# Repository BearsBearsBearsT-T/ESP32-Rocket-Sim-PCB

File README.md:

# ESP32-Rocket-Sim-PCB
An MPU and ESP32 powered PCB that tracks motion in real time useing an MPU 6050 and an ESP32-c3-wroom made in KICAD. This bored can senses movement, orientation, and rotation by reading accelerometer and gyroscope data from the MPU. I made this project to learn more about digital sensors and building somthing with out a tutorial. 

**What it does:**
- It uses the MPU 6050 to track motion and orientation and controld the orientation of a rocket graphic made in processing (soming soon)
- powerd by a USB-C (V2 might be whireless)
- Runs on ESP32

**Componants:**

- ESP32
- MPU6050
- USB-C
- Voltage regulator
- capasators

This was my 2nd ever PCB and I think this one is a really cool project. I like sensors alot and I like making hardware that interacts with software. 
This was my first PCB that was not from a tutorial and the process was suppriseingly intuative. 

# Pictures

# BOM

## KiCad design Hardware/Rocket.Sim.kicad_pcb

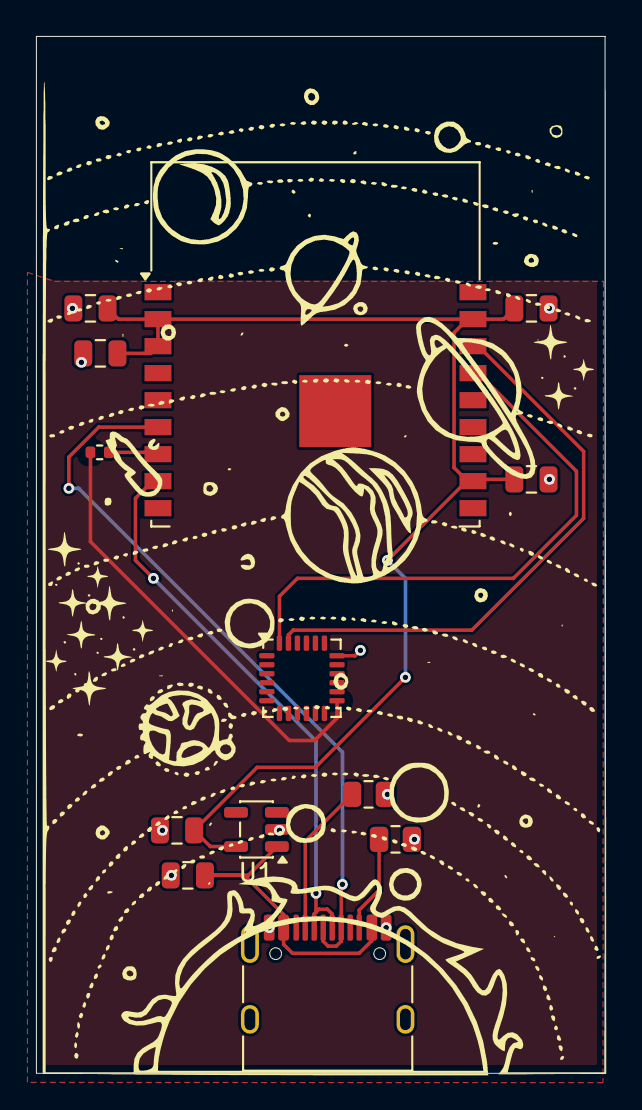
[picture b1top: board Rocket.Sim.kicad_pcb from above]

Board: 2 copper layers, 31.6 x 57.6 mm, 13 parts (0 on the bottom side), 11 nets.

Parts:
C1, C2: 10uf; C_0805_2012Metric
C3, C4, C5, C6: 0.1uf; C_0805_2012Metric
J1: USB_C_Receptacle_USB2.0_14P; USB_C_Receptacle_HRO_TYPE-C-31-M-12
R1, R2: 5.1kΩ; R_0805_2012Metric
R3: 10k; R_0402_1005Metric
U1: AP2112K-3.3; SOT-23-5
U2: MPU-6050; InvenSense_QFN-24_4x4mm_P0.5mm
U3: ESP32-C3; ESP-WROOM-02

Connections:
+3.3V: R3.2, U2.13 (VDD)
+3V3: C2.1, C3.2, C4.2, C5.2, C6.2, U1.5 (VOUT), U3.2 (VDD3P3), U3.3 (VDD3P3), U3.11 (VDD3P3_RTC), U3.17 (VDD3P3_CPU)
D+: J1.A6 (D+), J1.B6 (D+), U3.6 (GPIO2)
D-: J1.A7 (D-), J1.B7 (D-), U3.8 (GPIO3)
GND: C1.1, C2.2, C3.1, C4.1, C5.1, C6.1, J1.A1 (GND), J1.A12 (GND), J1.B1 (GND), J1.B12 (GND), R1.2, R2.2, U1.2 (GND), U2.18 (GND)
unnamed: J1.A5 (CC1), R1.1
unnamed: J1.B5 (CC2), R2.1
unnamed: R3.1, U3.7 (CHIP_EN)
PWR: C1.2, J1.A4 (VBUS), J1.A9 (VBUS), J1.B4 (VBUS), J1.B9 (VBUS), U1.1 (VIN)
SCL: U2.23 (SCL), U3.16 (GPIO10)
SDA: U2.24 (SDA), U3.15 (GPIO9)

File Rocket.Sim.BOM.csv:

"Reference","Qty","Value","DNP","Exclude from BOM","Exclude from Board","Footprint","Datasheet"
"C1,C2","2","10uf","","","","Capacitor_SMD:C_0805_2012Metric",""
"C3,C4,C5,C6","4","0.1uf","","","","Capacitor_SMD:C_0805_2012Metric",""
"J1","1","USB_C_Receptacle_USB2.0_14P","","","","Connector_USB:USB_C_Receptacle_HRO_TYPE-C-31-M-12","https://www.usb.org/sites/default/files/documents/usb_type-c.zip"
"R1,R2","2","5.1kΩ","","","","Resistor_SMD:R_0805_2012Metric",""
"R3","1","10k","","","","Resistor_SMD:R_0402_1005Metric",""
"U1","1","AP2112K-3.3","","","","Package_TO_SOT_SMD:SOT-23-5","https://www.diodes.com/assets/Datasheets/AP2112.pdf"
"U2","1","MPU-6050","","","","Sensor_Motion:InvenSense_QFN-24_4x4mm_P0.5mm","https://invensense.tdk.com/wp-content/uploads/2015/02/MPU-60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"
"U3","1","ESP32-C3","","","","RF_Module:ESP-WROOM-02","https://www.espressif.com/sites/default/files/documentation/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"

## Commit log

2026-05-02 Rename Rocket.Sim.kicad_pcb to Hardware/Rocket.Sim.kicad_pcb
2026-05-02 Rename Rocket.Sim.kicad_pro to Hardware/Rocket.Sim.kicad_pro
2026-05-02 Rename Rocket.Sim.kicad_sch to Hardware/Rocket.Sim.kicad_sch
2026-06-02 Rename ABX00162-cad-files (1).zip to Hardware/ABX00162-cad-files (1).zip
